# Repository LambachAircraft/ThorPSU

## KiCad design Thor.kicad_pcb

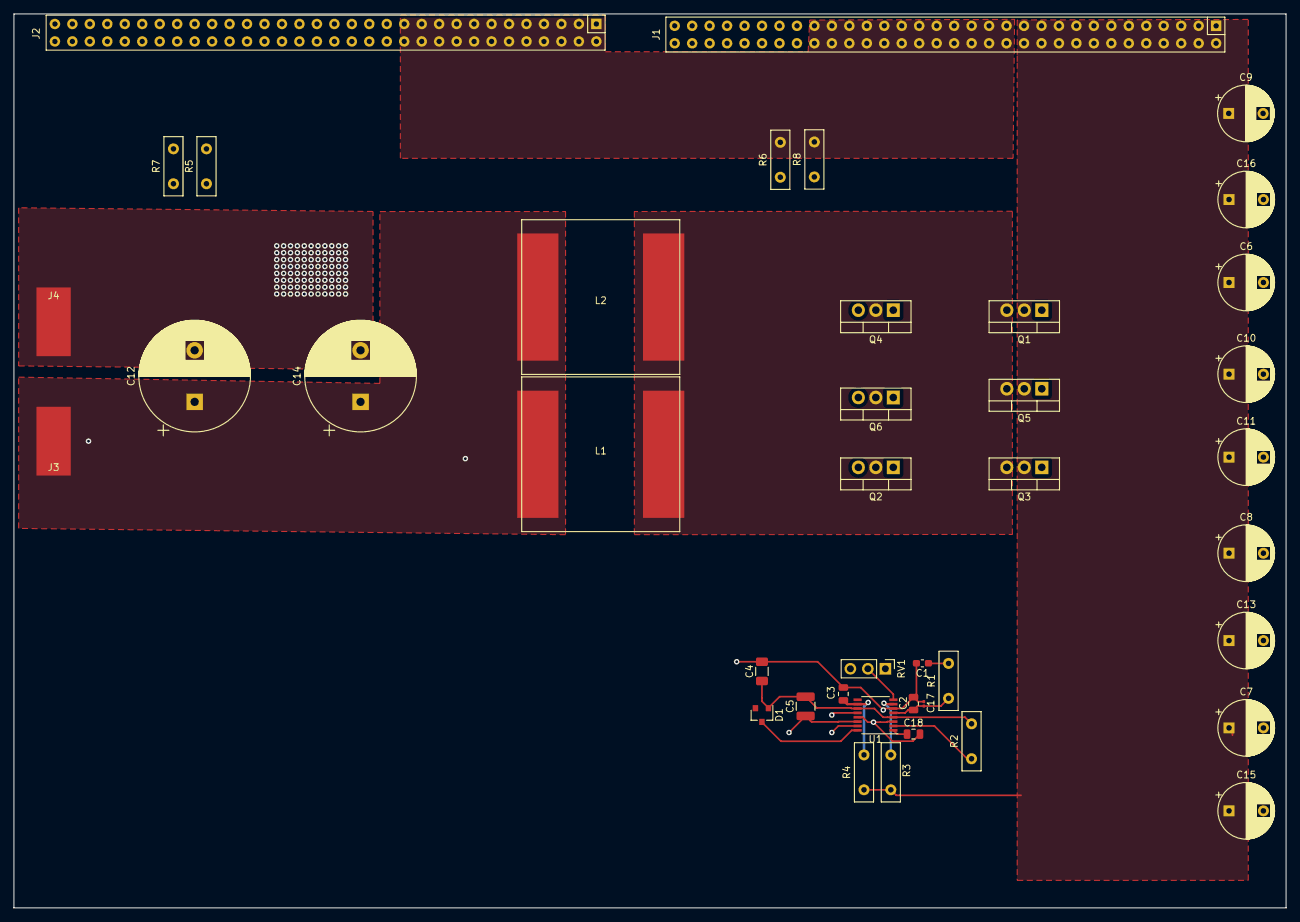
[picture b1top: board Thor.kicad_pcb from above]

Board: 4 copper layers, 185.0 x 130.0 mm, 41 parts (0 on the bottom side), 20 nets.

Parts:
C1: 2200pF; C_0603_1608Metric_Pad1.05x0.95mm_HandSolder
C2: 22pF; C_0805_2012Metric
C3, C18: 0.1uF; C_0805_2012Metric
C4: 4.7 uF; C_1206_3216Metric
C5: 0.47uF; C_1210_3225Metric
C6, C7, C8, C9, C10, C11, C13, C15, C16: 82uF; CP_Radial_D8.0mm_P5.00mm
C12, C14: 2200uF/50V; CP_Radial_D16.0mm_P7.50mm
C17: 22pF; C_0201_0603Metric
D1: ZLLS1000TA; D_SOT-23_ANK
J1, J2: Conn_02x32_Counter_Clockwise; HP DPS connector
J3, J4: Conn_01x01; SolderWirePad_1x01_SMD_5x10mm
L1, L2: 15uH; MPX1D2213
Q1, Q2, Q3, Q4, Q5, Q6: PHP79NQ08LT; TO-220-3_Vertical
R1: 22k; R_Box_L8.4mm_W2.5mm_P5.08mm
R2: 100k; R_Box_L8.4mm_W2.5mm_P5.08mm
R3: 8570k; R_Box_L8.4mm_W2.5mm_P5.08mm
R4: 2.2; R_Box_L8.4mm_W2.5mm_P5.08mm
R5, R6, R7, R8: 3.3 k; R_Box_L8.4mm_W2.5mm_P5.08mm
RV1: R_POT; PinHeader_1x03_P2.54mm_Vertical
U1: LTC3878; SSOP-16_3.9x4.9mm_P0.635mm

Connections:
/12V_IN: J1.13, J1.14, J1.15, J1.16, J1.17, J1.18, J1.19, J1.20, J1.21, J1.22, J1.23, J1.24, J1.41, J1.42, J1.43, J1.44, J1.45, J1.46, J1.47, J1.48, J1.49, J1.50, J1.51, J1.52, J2.1, J2.2, J2.3, J2.4, J2.5, J2.6, J2.7, J2.8, J2.9, J2.10, J2.11, J2.12, J2.53, J2.54, J2.55, J2.56, J2.57, J2.58, J2.59, J2.60, J2.61, J2.62, J2.63, J2.64, R6.2, R8.2
/BG: Q2.1, Q4.1, Q6.1, U1.12
/BOOST: D1.1, U1.16
/FCB: C4.1, C5.2, D1.2, R2.2, U1.4, U1.11
/Ion: R3.2, U1.7
/Ith: C2.1, C17.1, R1.1, U1.5
/MainPowerBus24V: C6.1, C7.1, C8.1, C9.1, C10.1, C11.1, C13.1, C15.1, C16.1, J1.1, J1.2, J1.3, J1.4, J1.5, J1.6, J1.7, J1.8, J1.9, J1.10, J1.11, J1.12, J1.53, J1.54, J1.55, J1.56, J1.57, J1.58, J1.59, J1.60, J1.61, J1.62, J1.63, J1.64, Q1.2, Q3.2, Q5.2, R3.1, R4.1
/OutPutPowerBus: C12.1, C14.1, J3.1, L1.2, L2.1, RV1.3
/PSU1_act: J1.31, J1.34
/PSU2_act: J2.31, J2.34
/PSU2_adj: J2.32, R5.1, R7.1
/PSU_V_adjust: J1.32, R6.1, R8.1
/Pgood: R2.1, U1.2
/RUNSS: C18.1, U1.1
/SW: C5.1, L1.1, L2.2, Q1.3, Q2.2, Q3.3, Q4.2, Q5.3, Q6.2, U1.14
/TG: Q1.1, Q3.1, Q5.1, U1.15
/Vfb: RV1.2, U1.8
/Vin: C3.2, R4.2, U1.10
GND: C1.2, C2.2, C3.1, C4.2, C6.2, C7.2, C8.2, C9.2, C10.2, C11.2, C12.2, C13.2, C14.2, C15.2, C16.2, C17.2, C18.2, J2.13, J2.14, J2.15, J2.16, J2.17, J2.18, J2.19, J2.20, J2.21, J2.22, J2.23, J2.24, J2.41, J2.42, J2.43, J2.44, J2.45, J2.46, J2.47, J2.48, J2.49, J2.50, J2.51, J2.52, J4.1, Q2.3, Q4.3, Q6.3, R5.2, R7.2, RV1.1, U1.3, U1.6, U1.13
unnamed: C1.1, R1.2

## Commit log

2020-03-04 added LTC3878
2020-03-04 schematic update
2020-03-10 update for Josh
2020-03-10 YOLO
2020-03-12 With PCB File
2020-03-17 added custom conn
2020-03-17 PCB Control Traces and Better Layout
2020-03-17 added custom connector to schematic
2020-03-17 Fixed connectors in PCB
2020-03-17 Card Connector Change and Locations Changed
2020-03-18 first complete layout with BIG Polygons
2020-03-24 most recent version
2020-03-24 Revert "most recent version"
    This reverts commit 98a59f1a5a33474df10b14d2ac29c781506322cc.
2020-03-24 Form factor change
